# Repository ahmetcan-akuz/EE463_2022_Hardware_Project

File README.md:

# EE463_Hardware_Project
This is a repository of EE 463 Hardware Project. This project is designed by Ahmetcan Akuz, Utku Deniz Altıok and Ekin Arda Çömez.

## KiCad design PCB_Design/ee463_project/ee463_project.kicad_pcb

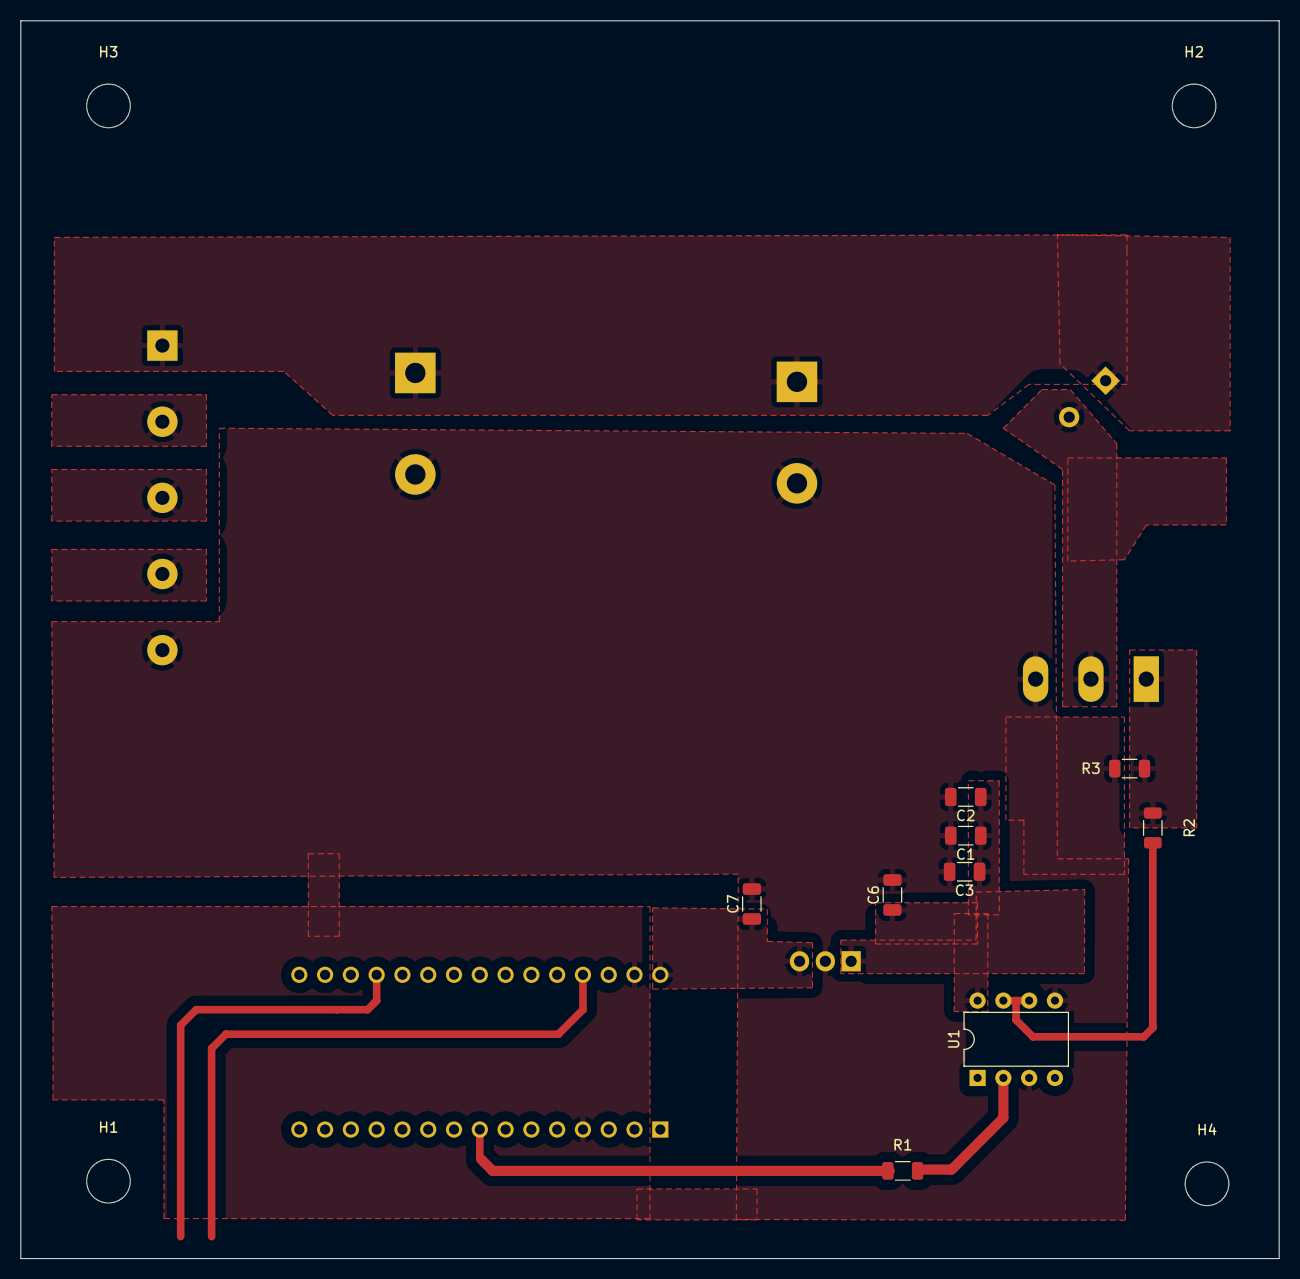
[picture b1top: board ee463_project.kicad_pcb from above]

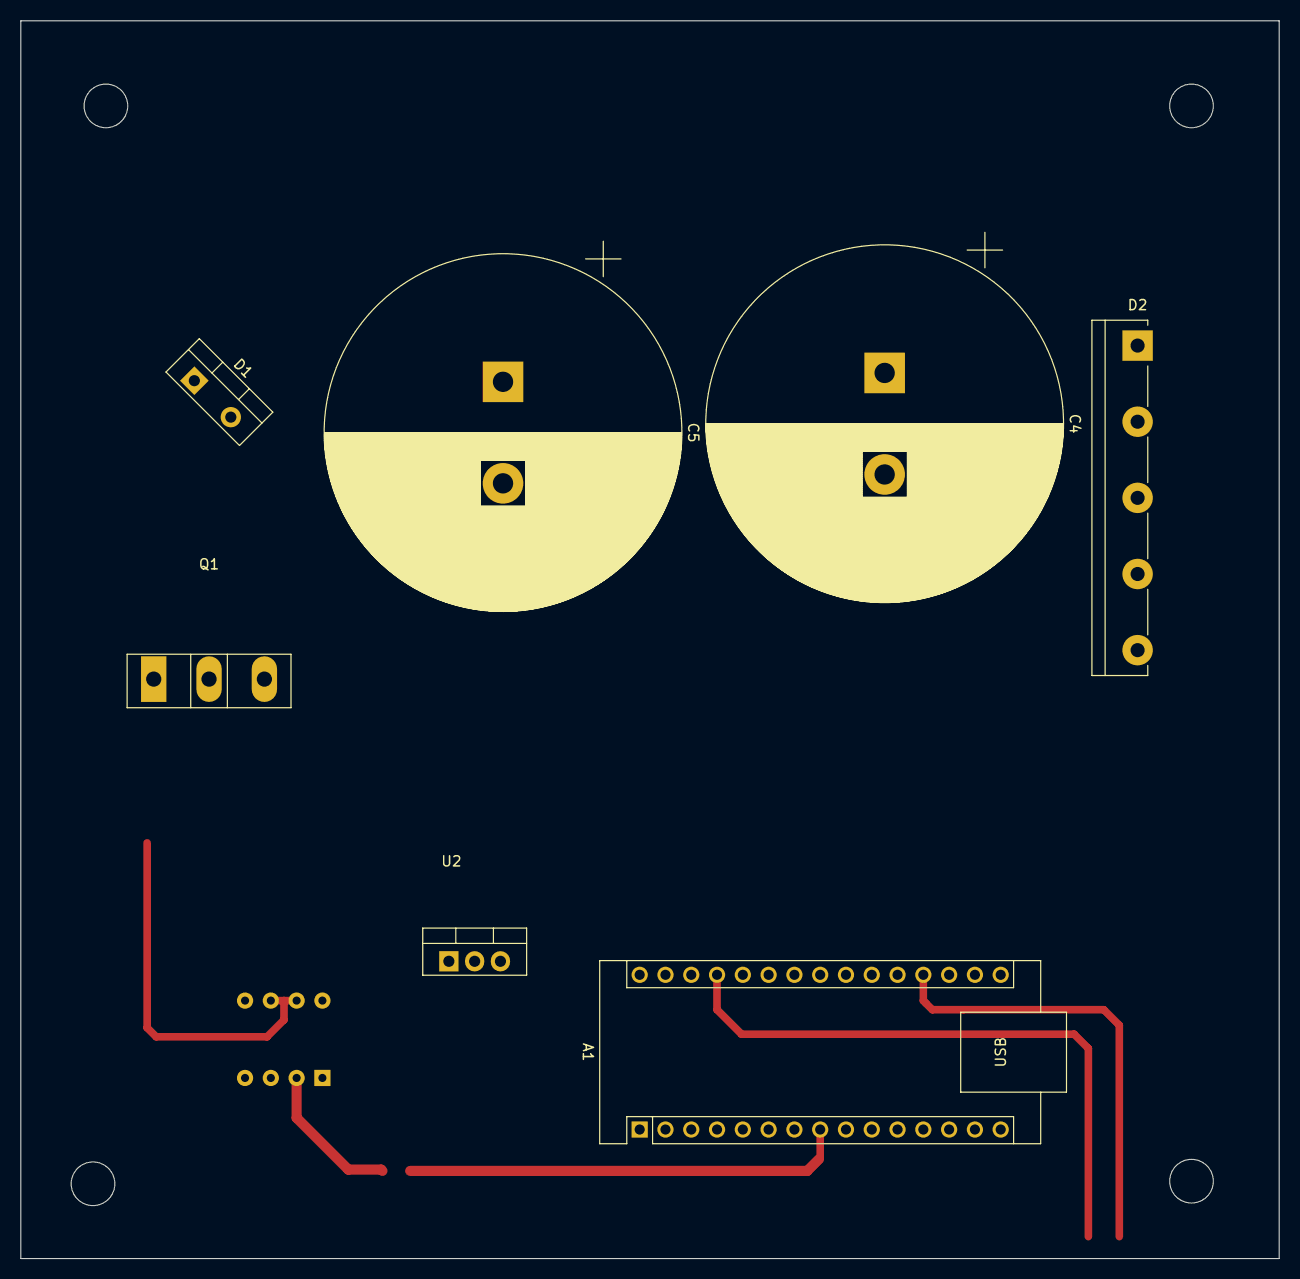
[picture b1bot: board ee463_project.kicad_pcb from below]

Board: 2 copper layers, 124.0 x 121.9 mm, 20 parts (7 on the bottom side), 9 nets.

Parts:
A1: Arduino_Nano_v2.x; Arduino_Nano
C1: 100n; C_1206_3216Metric
C2, C3: 10n; C_1206_3216Metric
C4, C5: 470u; CP_Radial_D35.0mm_P10.00mm_SnapIn
C6: 0.33u; C_1206_3216Metric
C7: 0.1u; C_1206_3216Metric
D1: BYV79-100; TO-220-2_Vertical
D2: GUO40-12NO1; Diode_Bridge_IXYS_GUFP
H1, H2, H3, H4: MountingHole; MountingHole_4.3mm_M4
Q1: C2M0080120D; TO-247-3_Vertical
R1: 510; R_1206_3216Metric
R2: 10; R_1206_3216Metric
R3: 10k; R_1206_3216Metric
U1: TLP250; DIP-8_W7.62mm
U2: L7808; TO-220-3_Vertical

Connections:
Drain: D1.2 (A), Q1.2 (D)
GND1: A1.4 (GND), A1.29 (GND), C1.2, C2.2, C3.2, C4.2, C5.2, C6.2, C7.2, D2.5 (-), Q1.3 (S), R3.2, U1.3 (C), U1.5 (VEE), U2.2 (GND)
Gate: Q1.1 (G), R2.2, R3.1
unnamed: R1.2, U1.2 (A)
unnamed: R2.1, U1.6 (VO), U1.7 (VO)
PWM: A1.8 (D5), R1.1
V_in_arduino: A1.30 (VIN), C7.1, U2.3 (OUT)
Vcc: C1.1, C2.1, C3.1, C6.1, U1.8 (VCC), U2.1 (IN)
Vout: C4.1, C5.1, D1.1 (K), D2.1 (+)

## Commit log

2022-12-03 Second Design
2022-12-03 3Phase Diode Rect+DC/DC Converter
    Three phase diode rectifier + DC/DC converter simulation was added.
2022-12-04 Motor Model of the Given Motor
    (We will consider about using the DC Machine Block as well)
2022-12-06 LM555 Astable Mode Simulation and Datasheet
    LM555 Astable Mode Simulation and Datasheet were added.
2022-12-06 Single Phase Thyristor Rectifier with filter
2022-12-06 Firing angle and LC filter updated.
    Firing angle has updated as 22 and output resistance has changed as 10 Ohm. Input voltage has also updated as 220Vrms
2022-12-06 LM555 LT Spice Simulation run
2022-12-06 Firing angle and output filter updated
2022-12-10 Three Phase Full Bridge + Buck with Motor Model at the end.
2022-12-11 Simulations Updated
2022-12-22 report
2022-12-22 Plexim Simulation Added
2022-12-23 We putted switching mosfet on the downside
2022-12-23 Low Side MOSFET Plexim Model
    Low Side MOSFET Plexim Model was added.
2022-12-24 TLP 250 Optocopuler Gate Driver Circuit
    We will use TLP250 as our non-inverting non-isolated gate driver circuit.
2022-12-24 Three Phase Full Bridge Diode Rectifier
2022-12-24 Si MOSFET FOR TRIAL PART
2022-12-24 TLP 250 Optocopuler Gate Driver Circuit
2022-12-24 THREE PHASE FULL BRIDGE RECTIFIER
2022-12-24 SiC Diode
2022-12-24 Aurdino PWM Generating Code
2022-12-25 Loss Calculation And Thermal Analysis
2022-12-27 Gate Driver Simulation
    Optocoupler is working properly. However\ there 's a problem with buck converter topology.
2022-12-27 Gate Driver Passive Updated
    Input resistance updated to 500 Ohm. R2 updated1k to 10k.
2022-12-27 TLP250 Info Doc Added
2022-12-27 Gate Driver Experiment Procedure Added
    This is a procedure to observe switching performance of TLP250.
2022-12-28 Gate Driver Updated
2023-01-03 LT Spice Buck Converter Topology Added
    Buck converter topology was added to gate driver concept in simulation
2023-01-03 PCB Design
    PCB Design of the project in KiCad was added.
2023-01-04 PCB Completed Gerber Files Added
2023-01-04 PCB Design Updated
2023-01-05 Only Soft Start
2023-01-05 PI and Soft Start
2023-01-05 PI in Cascade and Soft Start
2023-01-07 addition of PI controller
2023-01-08 Delete Aurdino_Codes directory
    Addin final version of arduino codes
2023-01-08 Final Version of Arduino Codes
2023-01-11 Improved Codes
2023-01-11 Codes Improved
2023-01-14 PCB Update
2023-01-20 Final on_off control
2023-01-22 Schematics
2023-01-22 pcb figures added
2023-01-22 Test Results were added.
2023-01-22 Test Results added
2023-01-22 Test result updated
2023-01-24 Test result figures were added
2023-01-24 Final Version of the Final Report
2023-01-25 Hardware Final Report was added.
